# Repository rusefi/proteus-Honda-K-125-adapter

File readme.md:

[Connector Pinout Spreadhseet, with links to wiring drawings](https://docs.google.com/spreadsheets/d/1G6FDarE99hbd0HSs6bh5kEkZy6p-kYTxa0NcJpE1HUc)

Part of https://github.com/rusefi/rusefi/wiki/Proteus#adapters family

https://github.com/rusefi/rusefi/wiki/Proteus-Honda125

https://www.ebay.com/itm/334206656537

First test mule https://rusefi.com/forum/viewtopic.php?f=2&t=1955

https://github.com/rusefi/rusefi/wiki/Vault-Of-Honda-OEM#dbc-k

https://github.com/rusefi/rusefi/wiki/Honda-Element

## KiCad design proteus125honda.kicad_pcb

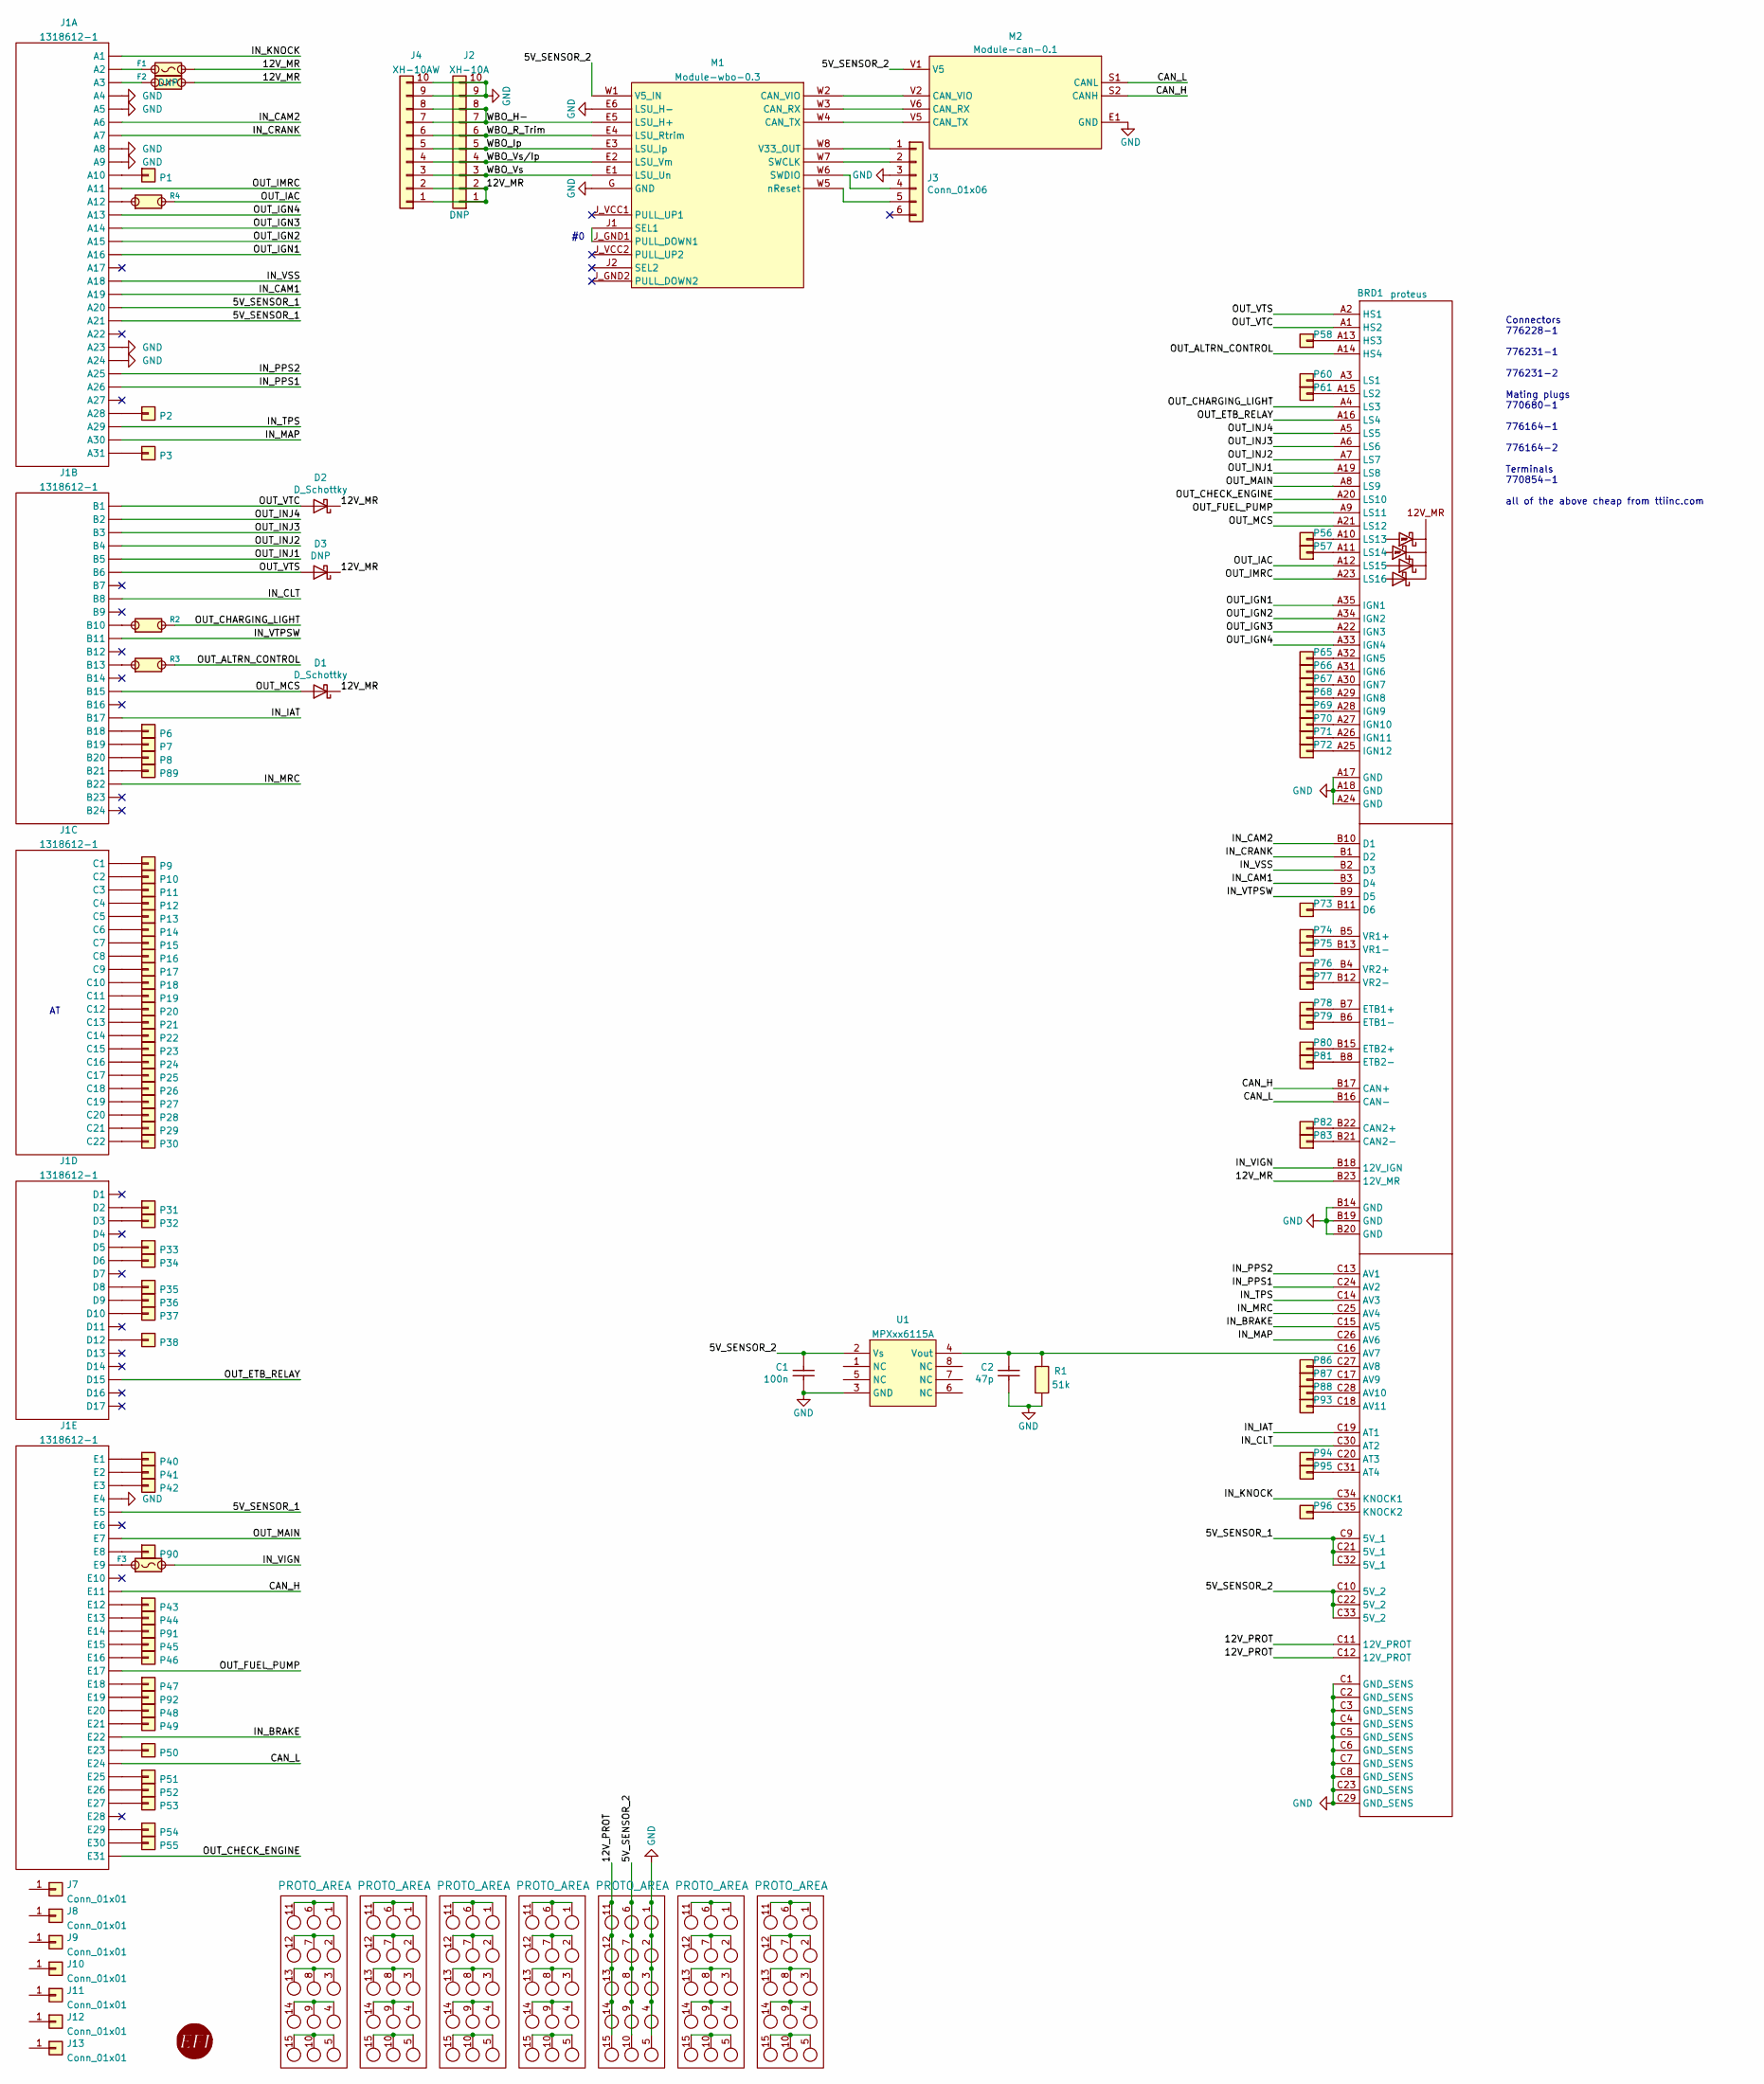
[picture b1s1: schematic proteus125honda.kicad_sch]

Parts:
BRD1: proteus
C1: 100n; C0603; LCSC C14663
C2: 47p; C0603; LCSC C1671
D1, D2: D_Schottky; D_SMA; LCSC C8678
D3: DNP; D_SMA
F1, F3: Fuse-Pad-Pad; PAD-1206-PAD; LCSC C182446
F2: Fuse-Pad-Pad; PAD-1206-PAD
G1, G2, G3, G4, G5, G7, G8: PROTO_AREA
G6: RUSEFI_LOGO; rusefi_logo
J1: 1318612-1; TE_1318612-1
J2: XH-10A; JST_XH_B10B-XH-A_1x10_P2.50mm_Vertical; LCSC C8885
J3: Conn_01x06; PinHeader_1x06_P2.54mm_Vertical
J4: XH-10AW; JST_XH_S10B-XH-A_1x10_P2.50mm_Horizontal; LCSC C14652
J7, J8, J9, J10, J11, J12, J13: Conn_01x01; MountingHole_4.5mm
M1: Module-wbo-0.3; wbo
M2: Module-can-0.1; can
P1, P2, P3, P6, P7, P8, P9, P10, P11, P12, P13, P14, P15, P16, P17, P18, P19, P20, P21, P22, P23, P24, P25, P26, P27, P28, P29, P30, P31, P32, P33, P34, P35, P36, P37, P38, P40, P41, P42, P43, P44, P45, P46, P47, P48, P49, P50, P51, P52, P53, P54, P55, P56, P57, P58, P60, P61, P65, P66, P67, P68, P69, P70, P71, P72, P73, P74, P75, P76, P77, P78, P79, P80, P81, P82, P83, P86, P87, P88, P89, P90, P91, P92, P93, P94, P95, P96: Pad; PAD-TH
R1: 51k; R0603; LCSC C23196
R2, R3, R4: Jumper-Pad-Pad; PAD-0805-PAD; LCSC C17477
U1: MPXxx6115A; MPX_SOP_SSOP

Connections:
/5V_SENSOR_1: BRD1.C9 (5V_1), BRD1.C21 (5V_1), BRD1.C32 (5V_1), J1.A20, J1.A21, J1.E5
/5V_SENSOR_2: BRD1.C10 (5V_2), BRD1.C22 (5V_2), BRD1.C33 (5V_2), C1.2, G5.6, G5.7, G5.8, G5.9, G5.10, M1.W1 (V5_IN), M2.V1 (V5), U1.2 (Vs)
/12V_MR: BRD1.B23 (12V_MR), D1.1 (K), D2.1 (K), D3.1 (K), F1.2, F2.2, J2.1, J2.2, J4.1, J4.2
/12V_PROT: BRD1.C11 (12V_PROT), BRD1.C12 (12V_PROT), G5.11, G5.12, G5.13, G5.14, G5.15
/CAN_H: BRD1.B17 (CAN+), J1.E11, M2.S2 (CANH)
/CAN_L: BRD1.B16 (CAN-), J1.E24, M2.S1 (CANL)
/IN_BRAKE: BRD1.C15 (AV5), J1.E22
/IN_CAM1: BRD1.B3 (D4), J1.A19
/IN_CAM2: BRD1.B10 (D1), J1.A6
/IN_CLT: BRD1.C30 (AT2), J1.B8
/IN_CRANK: BRD1.B1 (D2), J1.A7
/IN_IAT: BRD1.C19 (AT1), J1.B17
/IN_KNOCK: BRD1.C34 (KNOCK1), J1.A1
/IN_MAP: BRD1.C26 (AV6), J1.A30
/IN_MRC: BRD1.C25 (AV4), J1.B22
/IN_PPS1: BRD1.C24 (AV2), J1.A26
/IN_PPS2: BRD1.C13 (AV1), J1.A25
/IN_TPS: BRD1.C14 (AV3), J1.A29
/IN_VIGN: BRD1.B18 (12V_IGN), F3.2
/IN_VSS: BRD1.B2 (D3), J1.A18
/IN_VTPSW: BRD1.B9 (D5), J1.B11
/OUT_ALTRN_CONTROL: BRD1.A14 (HS4), R3.2
/OUT_CHARGING_LIGHT: BRD1.A4 (LS3), R2.2
/OUT_CHECK_ENGINE: BRD1.A20 (LS10), J1.E31
/OUT_ETB_RELAY: BRD1.A16 (LS4), J1.D15
/OUT_FUEL_PUMP: BRD1.A9 (LS11), J1.E17
/OUT_IAC: BRD1.A12 (LS15), R4.2
/OUT_IGN1: BRD1.A35 (IGN1), J1.A16
/OUT_IGN2: BRD1.A34 (IGN2), J1.A15
/OUT_IGN3: BRD1.A22 (IGN3), J1.A14
/OUT_IGN4: BRD1.A33 (IGN4), J1.A13
/OUT_IMRC: BRD1.A23 (LS16), J1.A11
/OUT_INJ1: BRD1.A19 (LS8), J1.B5
/OUT_INJ2: BRD1.A7 (LS7), J1.B4
/OUT_INJ3: BRD1.A6 (LS6), J1.B3
/OUT_INJ4: BRD1.A5 (LS5), J1.B2
/OUT_MAIN: BRD1.A8 (LS9), J1.E7
/OUT_MCS: BRD1.A21 (LS12), D1.2 (A), J1.B15
/OUT_VTC: BRD1.A1 (HS2), D2.2 (A), J1.B1
/OUT_VTS: BRD1.A2 (HS1), D3.2 (A), J1.B6
/WBO_H-: J2.7, J2.8, J4.7, J4.8, M1.E5 (LSU_H+)
/WBO_Ip: J2.5, J4.5, M1.E3 (LSU_Ip)
/WBO_R_Trim: J2.6, J4.6, M1.E4 (LSU_Rtrim)
/WBO_Vs: J2.3, J4.3, M1.E1 (LSU_Un)
/WBO_Vs/Ip: J2.4, J4.4, M1.E2 (LSU_Vm)
GND: BRD1.A17 (GND), BRD1.A18 (GND), BRD1.A24 (GND), BRD1.B14 (GND), BRD1.B19 (GND), BRD1.B20 (GND), BRD1.C1 (GND_SENS), BRD1.C2 (GND_SENS), BRD1.C3 (GND_SENS), BRD1.C4 (GND_SENS), BRD1.C5 (GND_SENS), BRD1.C6 (GND_SENS), BRD1.C7 (GND_SENS), BRD1.C8 (GND_SENS), BRD1.C23 (GND_SENS), BRD1.C29 (GND_SENS), C1.1, C2.1, G5.1, G5.2, G5.3, G5.4, G5.5, J1.A4, J1.A5, J1.A8, J1.A9, J1.A23, J1.A24, J1.E4, J2.9, J2.10, J3.3, J4.9, J4.10, M1.E6 (LSU_H-), M1.G (GND), M2.E1 (GND), R1.2, U1.3 (GND)
unnamed: BRD1.A3 (LS1), P60.1
unnamed: BRD1.A10 (LS13), P56.1
unnamed: BRD1.A11 (LS14), P57.1
unnamed: BRD1.A13 (HS3), P58.1
unnamed: BRD1.A15 (LS2), P61.1
unnamed: BRD1.A25 (IGN12), P72.1
unnamed: BRD1.A26 (IGN11), P71.1
unnamed: BRD1.A27 (IGN10), P70.1
unnamed: BRD1.A28 (IGN9), P69.1
unnamed: BRD1.A29 (IGN8), P68.1
unnamed: BRD1.A30 (IGN7), P67.1
unnamed: BRD1.A31 (IGN6), P66.1
unnamed: BRD1.A32 (IGN5), P65.1
unnamed: BRD1.B4 (VR2+), P76.1
unnamed: BRD1.B5 (VR1+), P74.1
unnamed: BRD1.B6 (ETB1-), P79.1
unnamed: BRD1.B7 (ETB1+), P78.1
unnamed: BRD1.B8 (ETB2-), P81.1
unnamed: BRD1.B11 (D6), P73.1
unnamed: BRD1.B12 (VR2-), P77.1
unnamed: BRD1.B13 (VR1-), P75.1
unnamed: BRD1.B15 (ETB2+), P80.1
unnamed: BRD1.B21 (CAN2-), P83.1
unnamed: BRD1.B22 (CAN2+), P82.1
unnamed: BRD1.C16 (AV7), C2.2, R1.1, U1.4 (Vout)
unnamed: BRD1.C17 (AV9), P87.1
unnamed: BRD1.C18 (AV11), P93.1
unnamed: BRD1.C20 (AT3), P94.1
unnamed: BRD1.C27 (AV8), P86.1
unnamed: BRD1.C28 (AV10), P88.1
unnamed: BRD1.C31 (AT4), P95.1
unnamed: BRD1.C35 (KNOCK2), P96.1
unnamed: F1.1, J1.A2
unnamed: F2.1, J1.A3
unnamed: F3.1, J1.E9
unnamed: G1.1, G1.6, G1.11
unnamed: G1.5, G1.10, G1.15
unnamed: G1.2, G1.7, G1.12
unnamed: G1.3, G1.8, G1.13
unnamed: G1.4, G1.9, G1.14
unnamed: G2.1, G2.6, G2.11
unnamed: G2.5, G2.10, G2.15
unnamed: G2.2, G2.7, G2.12
unnamed: G2.3, G2.8, G2.13
unnamed: G2.4, G2.9, G2.14
unnamed: G3.1, G3.6, G3.11
unnamed: G3.5, G3.10, G3.15
unnamed: G3.2, G3.7, G3.12
unnamed: G3.3, G3.8, G3.13
unnamed: G3.4, G3.9, G3.14
unnamed: G4.1, G4.6, G4.11
unnamed: G4.5, G4.10, G4.15
unnamed: G4.2, G4.7, G4.12
unnamed: G4.3, G4.8, G4.13
unnamed: G4.4, G4.9, G4.14
unnamed: G7.1, G7.6, G7.11
unnamed: G7.5, G7.10, G7.15
unnamed: G7.2, G7.7, G7.12
unnamed: G7.3, G7.8, G7.13
unnamed: G7.4, G7.9, G7.14
unnamed: G8.1, G8.6, G8.11
unnamed: G8.5, G8.10, G8.15
unnamed: G8.2, G8.7, G8.12
unnamed: G8.3, G8.8, G8.13
unnamed: G8.4, G8.9, G8.14
unnamed: J1.A10, P1.1
unnamed: J1.A12, R4.1
unnamed: J1.A28, P2.1
unnamed: J1.A31, P3.1
unnamed: J1.B10, R2.1
unnamed: J1.B13, R3.1
unnamed: J1.B18, P6.1
unnamed: J1.B19, P7.1
unnamed: J1.B20, P8.1
unnamed: J1.B21, P89.1
unnamed: J1.C1, P9.1
unnamed: J1.C2, P10.1
unnamed: J1.C3, P11.1
unnamed: J1.C4, P12.1
unnamed: J1.C5, P13.1
unnamed: J1.C6, P14.1
unnamed: J1.C7, P15.1
unnamed: J1.C8, P16.1
unnamed: J1.C9, P17.1
unnamed: J1.C10, P18.1
unnamed: J1.C11, P19.1
unnamed: J1.C12, P20.1
unnamed: J1.C13, P21.1
unnamed: J1.C14, P22.1
unnamed: J1.C15, P23.1
unnamed: J1.C16, P24.1
unnamed: J1.C17, P25.1
unnamed: J1.C18, P26.1
unnamed: J1.C19, P27.1
unnamed: J1.C20, P28.1
unnamed: J1.C21, P29.1
unnamed: J1.C22, P30.1
unnamed: J1.D2, P31.1
unnamed: J1.D3, P32.1
unnamed: J1.D5, P33.1
unnamed: J1.D6, P34.1
unnamed: J1.D8, P35.1
unnamed: J1.D9, P36.1
unnamed: J1.D10, P37.1
unnamed: J1.D12, P38.1
unnamed: J1.E1, P40.1
unnamed: J1.E2, P41.1
unnamed: J1.E3, P42.1
unnamed: J1.E8, P90.1
unnamed: J1.E12, P43.1
unnamed: J1.E13, P44.1
unnamed: J1.E14, P91.1
unnamed: J1.E15, P45.1
unnamed: J1.E16, P46.1
unnamed: J1.E18, P47.1
unnamed: J1.E19, P92.1
unnamed: J1.E20, P48.1
unnamed: J1.E21, P49.1
unnamed: J1.E23, P50.1
unnamed: J1.E25, P51.1
unnamed: J1.E26, P52.1
unnamed: J1.E27, P53.1
unnamed: J1.E29, P54.1
unnamed: J1.E30, P55.1
unnamed: J3.1, M1.W8 (V33_OUT)
unnamed: J3.2, M1.W7 (SWCLK)
unnamed: J3.4, M1.W6 (SWDIO)
unnamed: J3.5, M1.W5 (nReset)
unnamed: M1.J1 (SEL1), M1.J_GND1 (PULL_DOWN1)
unnamed: M1.W2 (CAN_VIO), M2.V2 (CAN_VIO)
unnamed: M1.W3 (CAN_RX), M2.V6 (CAN_RX)
unnamed: M1.W4 (CAN_TX), M2.V5 (CAN_TX)

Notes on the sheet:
Connectors 776228-1 776231-1 776231-2 Mating plugs 770680-1 776164-1 776164-2 Terminals 770854-1 all of the above cheap from ttiinc.com

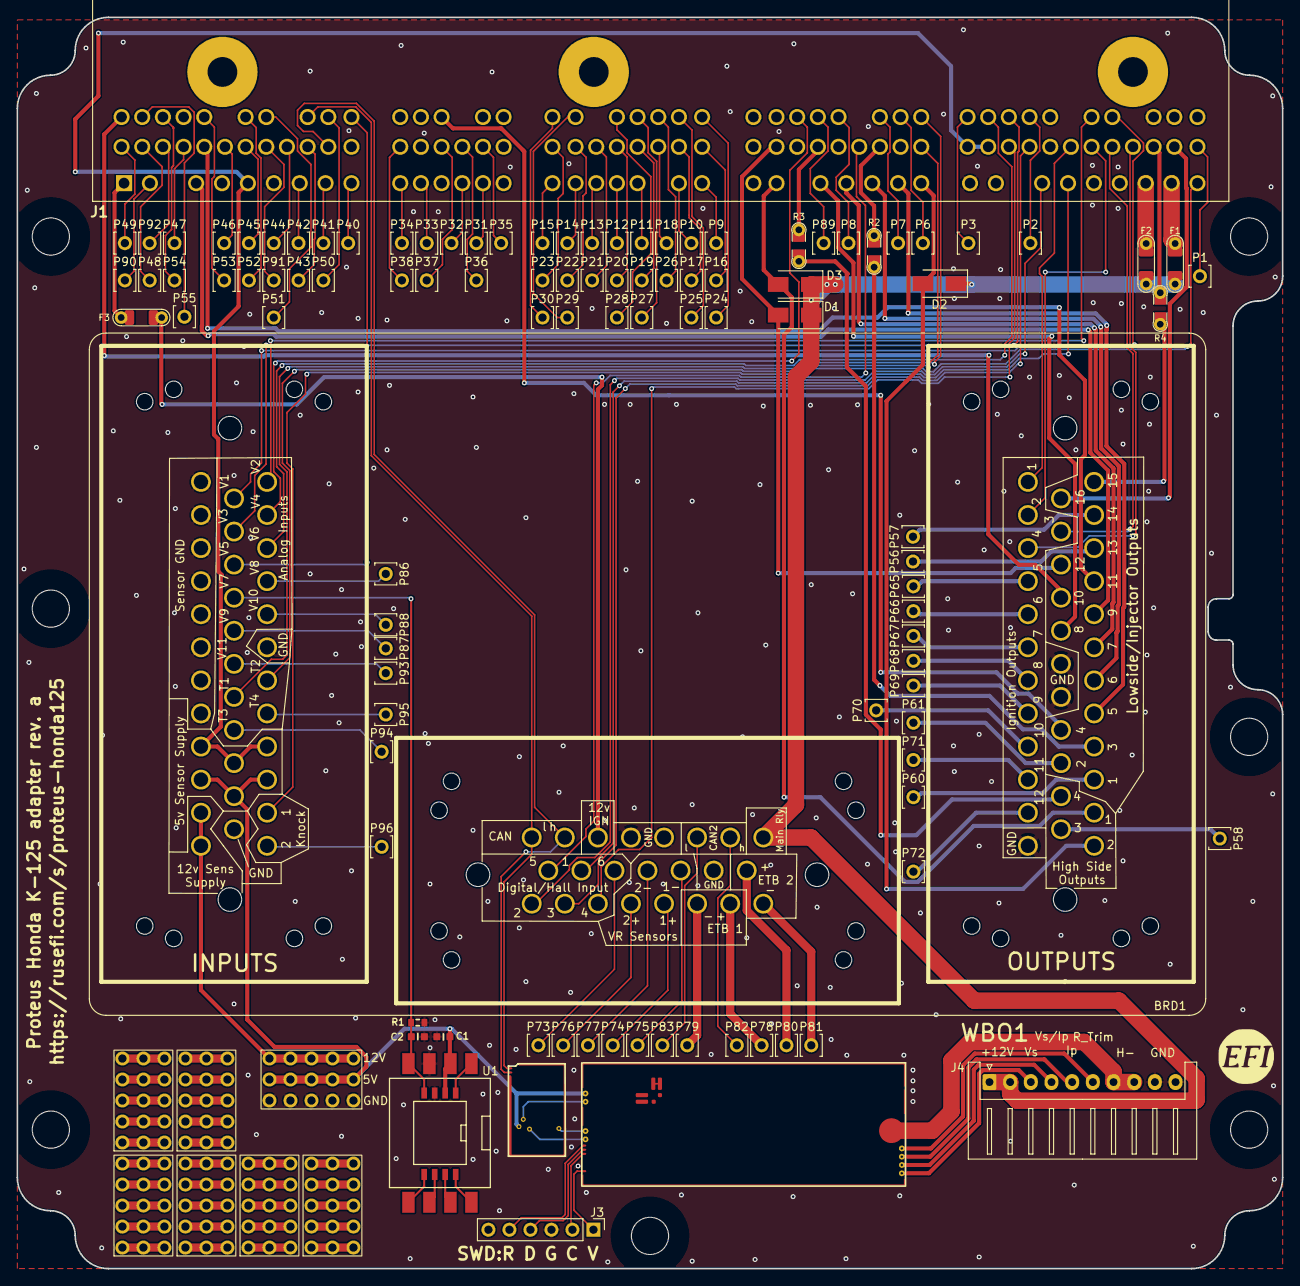
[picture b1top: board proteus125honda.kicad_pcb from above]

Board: 2 copper layers, 153.0 x 151.3 mm, 121 parts (0 on the bottom side), 178 nets.

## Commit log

2021-09-22 Connectors
2021-09-24 Upd pinout
2021-09-28 Upd pcb
2021-09-30 Proteus-compatible component
2021-09-30 Proteus-compatible board preview
2021-10-01 Fix proteus
2021-10-02 Export
2021-10-03 #17, #18, #14, #13
2021-10-09 update hellen-one and rename/move some files
2021-10-09 update gerber path in kicad files
2021-10-09 copy & create scripts, initial version
2021-10-11 Fresh outputs
2021-10-11 Fab time?
